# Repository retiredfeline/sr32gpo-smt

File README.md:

# Shift register 32 general purpose output board

These are the Kicad design files for the Shift register 32 bit general purpose output board described in my [Hackaday project page](https://hackaday.io/project/184239-3-line-to-32-line-output-expander).

## Versioning

SMT version February 2025

This version has been tested after assembly by PCBWay, who I thank for sponsoring a batch. You can find an uploaded project zip in the pcbway directory.

## Notes

The minimum lines required to use this board are: GND, SER (data), SRCLK (shift), RCLK (strobe). Vcc depends on the power arrangement. You should jumper the ~OESEL (output enable select) to ground if you don't wish to disable the display by signal, or vary the output with PWM, from a controller. The ~SRCLR input is only needed for resetting the output by the controller.

This board is designed with optional aspects you can choose to include or not:

- As mentioned some lines don't need to be driven in smaller configurations.

- Between 1 and 4 74HC595s can be installed for 8-32 outputs, in steps of 8. Naturally only the resistors for the used outputs need to be installed.

- The 74HC595 can source or sink 6 mA current.

- The 74HC595 can operate between 2V and 6V. This can be chosen to suit the controller, e.g. 3.3V or 5V, and the power supply section if installed.

- The power supply section is optional. You can choose to power this from the controller. Or you could power the controller with this.

- Copper pads for data and output are duplicated so you can attach more connectors or even solder wires. The input power is also brought out to duplicate pads for piggybacking to other circuits, e.g. an auxiliary board.

- Although the connectors are rendered as vertical pin headers, you can use other kinds of connectors like pin sockets, or even solder wires to the pads.

- You may wish to change the resistor to suit your application if you are getting the PCB assembled by editing the BoM. Currently it's set to 4.7k.

## Authors

* **Ken Yap**

## License

See the [LICENSE](LICENSE.md) file for license rights and limitations (MIT).

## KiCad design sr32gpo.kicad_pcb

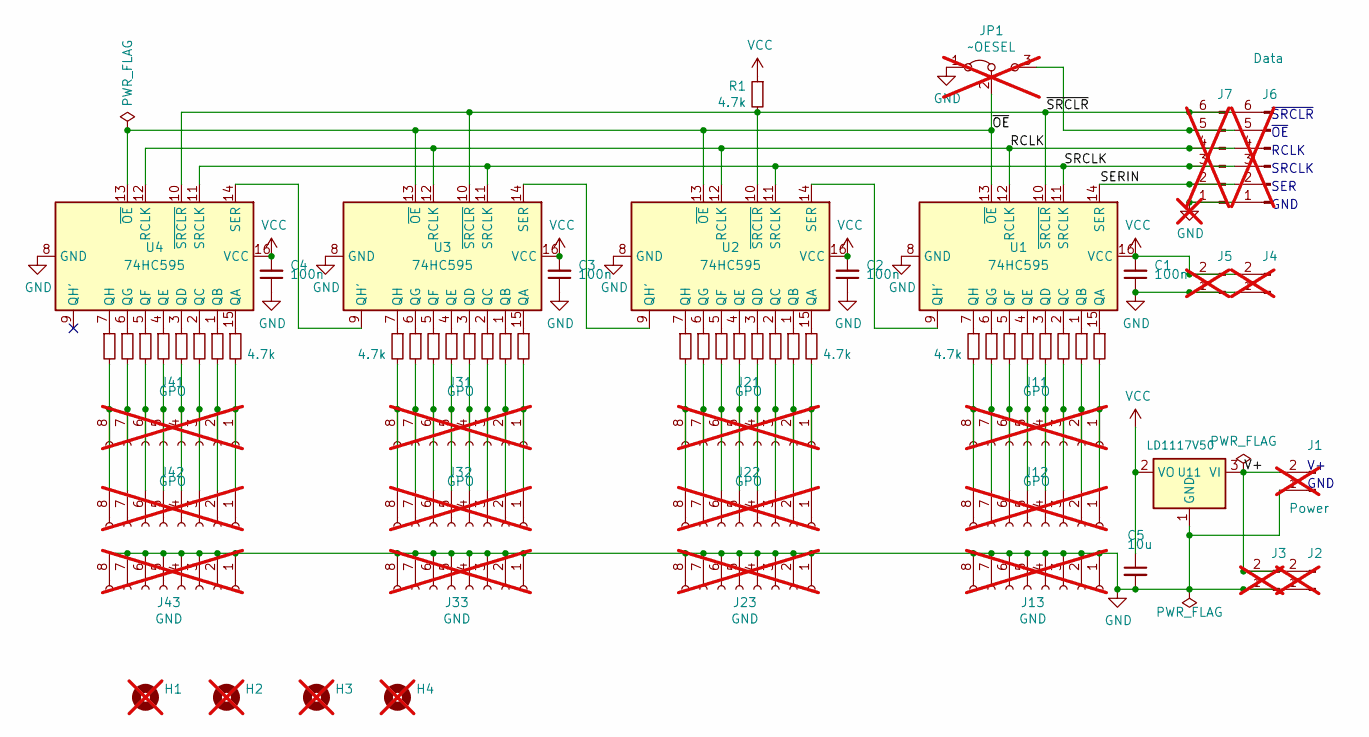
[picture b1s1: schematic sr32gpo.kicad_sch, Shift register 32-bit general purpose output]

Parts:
C1, C2, C3, C4: 100n; C_0603_1608Metric
C5: 10u; C_0805_2012Metric
H1, H2, H3, H4: MountingHole_3mm_Pad; not fitted
J1: Power; TerminalBlock_bornier-2_P5.08mm; not fitted
J2, J3, J4, J5: Power; PinHeader_1x02_P2.54mm_Vertical; not fitted
J6, J7: Data; PinHeader_1x06_P2.54mm_Vertical; not fitted
J11, J12, J21, J22, J31, J32, J41, J42: GPO; PinHeader_1x08_P2.54mm_Vertical; not fitted
J13, J23, J33, J43: GND; PinHeader_1x08_P2.54mm_Vertical; not fitted
JP1: ~OESEL; PinHeader_1x03_P2.54mm_Vertical; not fitted
R1, R11, R12, R13, R14, R15, R16, R17, R18, R21, R22, R23, R24, R25, R26, R27, R28, R31, R32, R33, R34, R35, R36, R37, R38, R41, R42, R43, R44, R45, R46, R47, R48: 4.7k; R_0603_1608Metric
U1, U2, U3, U4: 74HC595; SOIC-16_3.9x9.9mm_P1.27mm
U11: LD1117V50; SOT-223-3_TabPin2

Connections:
/RCLK: J6.4, J7.4, U1.12 (RCLK), U2.12 (RCLK), U3.12 (RCLK), U4.12 (RCLK)
/SERIN: J6.2, J7.2, U1.14 (SER)
/SRCLK: J6.3, J7.3, U1.11 (SRCLK), U2.11 (SRCLK), U3.11 (SRCLK), U4.11 (SRCLK)
/V+: J1.2, J2.2, J3.2, U11.3 (VI)
/~OE: JP1.2 (C), U1.13 (~OE), U2.13 (~OE), U3.13 (~OE), U4.13 (~OE)
/~SRCLR: J6.6, J7.6, R1.2, U1.10 (~SRCLR), U2.10 (~SRCLR), U3.10 (~SRCLR), U4.10 (~SRCLR)
GND: C1.1, C2.1, C3.1, C4.1, C5.2, J1.1, J2.1, J3.1, J4.1, J5.1, J6.1, J7.1, J13.1, J13.2, J13.3, J13.4, J13.5, J13.6, J13.7, J13.8, J23.1, J23.2, J23.3, J23.4, J23.5, J23.6, J23.7, J23.8, J33.1, J33.2, J33.3, J33.4, J33.5, J33.6, J33.7, J33.8, J43.1, J43.2, J43.3, J43.4, J43.5, J43.6, J43.7, J43.8, JP1.1 (A), U1.8 (GND), U2.8 (GND), U3.8 (GND), U4.8 (GND), U11.1 (GND)
unnamed: J6.5, J7.5, JP1.3 (B)
unnamed: J11.1, J12.1, R11.2
unnamed: J11.2, J12.2, R12.2
unnamed: J11.3, J12.3, R13.2
unnamed: J11.4, J12.4, R14.2
unnamed: J11.5, J12.5, R15.2
unnamed: J11.6, J12.6, R16.2
unnamed: J11.7, J12.7, R17.2
unnamed: J11.8, J12.8, R18.2
unnamed: J21.1, J22.1, R21.2
unnamed: J21.2, J22.2, R22.2
unnamed: J21.3, J22.3, R23.2
unnamed: J21.4, J22.4, R24.2
unnamed: J21.5, J22.5, R25.2
unnamed: J21.6, J22.6, R26.2
unnamed: J21.7, J22.7, R27.2
unnamed: J21.8, J22.8, R28.2
unnamed: J31.1, J32.1, R31.2
unnamed: J31.2, J32.2, R32.2
unnamed: J31.3, J32.3, R33.2
unnamed: J31.4, J32.4, R34.2
unnamed: J31.5, J32.5, R35.2
unnamed: J31.6, J32.6, R36.2
unnamed: J31.7, J32.7, R37.2
unnamed: J31.8, J32.8, R38.2
unnamed: J41.1, J42.1, R41.2
unnamed: J41.2, J42.2, R42.2
unnamed: J41.3, J42.3, R43.2
unnamed: J41.4, J42.4, R44.2
unnamed: J41.5, J42.5, R45.2
unnamed: J41.6, J42.6, R46.2
unnamed: J41.7, J42.7, R47.2
unnamed: J41.8, J42.8, R48.2
unnamed: R11.1, U1.15 (QA)
unnamed: R12.1, U1.1 (QB)
unnamed: R13.1, U1.2 (QC)
unnamed: R14.1, U1.3 (QD)
unnamed: R15.1, U1.4 (QE)
unnamed: R16.1, U1.5 (QF)
unnamed: R17.1, U1.6 (QG)
unnamed: U1.9 (QH'), U2.14 (SER)
unnamed: R18.1, U1.7 (QH)
unnamed: R21.1, U2.15 (QA)
unnamed: R22.1, U2.1 (QB)
unnamed: R23.1, U2.2 (QC)
unnamed: R24.1, U2.3 (QD)
unnamed: R25.1, U2.4 (QE)
unnamed: R26.1, U2.5 (QF)
unnamed: R27.1, U2.6 (QG)
unnamed: U2.9 (QH'), U3.14 (SER)
unnamed: R28.1, U2.7 (QH)
unnamed: R31.1, U3.15 (QA)
unnamed: R32.1, U3.1 (QB)
unnamed: R33.1, U3.2 (QC)
unnamed: R34.1, U3.3 (QD)
unnamed: R35.1, U3.4 (QE)
unnamed: R36.1, U3.5 (QF)
unnamed: R37.1, U3.6 (QG)
unnamed: U3.9 (QH'), U4.14 (SER)
unnamed: R38.1, U3.7 (QH)
unnamed: R41.1, U4.15 (QA)
unnamed: R42.1, U4.1 (QB)
unnamed: R43.1, U4.2 (QC)
unnamed: R44.1, U4.3 (QD)
unnamed: R45.1, U4.4 (QE)
unnamed: R46.1, U4.5 (QF)
unnamed: R47.1, U4.6 (QG)
unnamed: R48.1, U4.7 (QH)
VCC: C1.2, C2.2, C3.2, C4.2, C5.1, J4.2, J5.2, R1.1, U1.16 (VCC), U2.16 (VCC), U3.16 (VCC), U4.16 (VCC), U11.2 (VO)

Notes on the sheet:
RCLK
SRCLK
GND
~{OE}
~{SRCLR}
SER

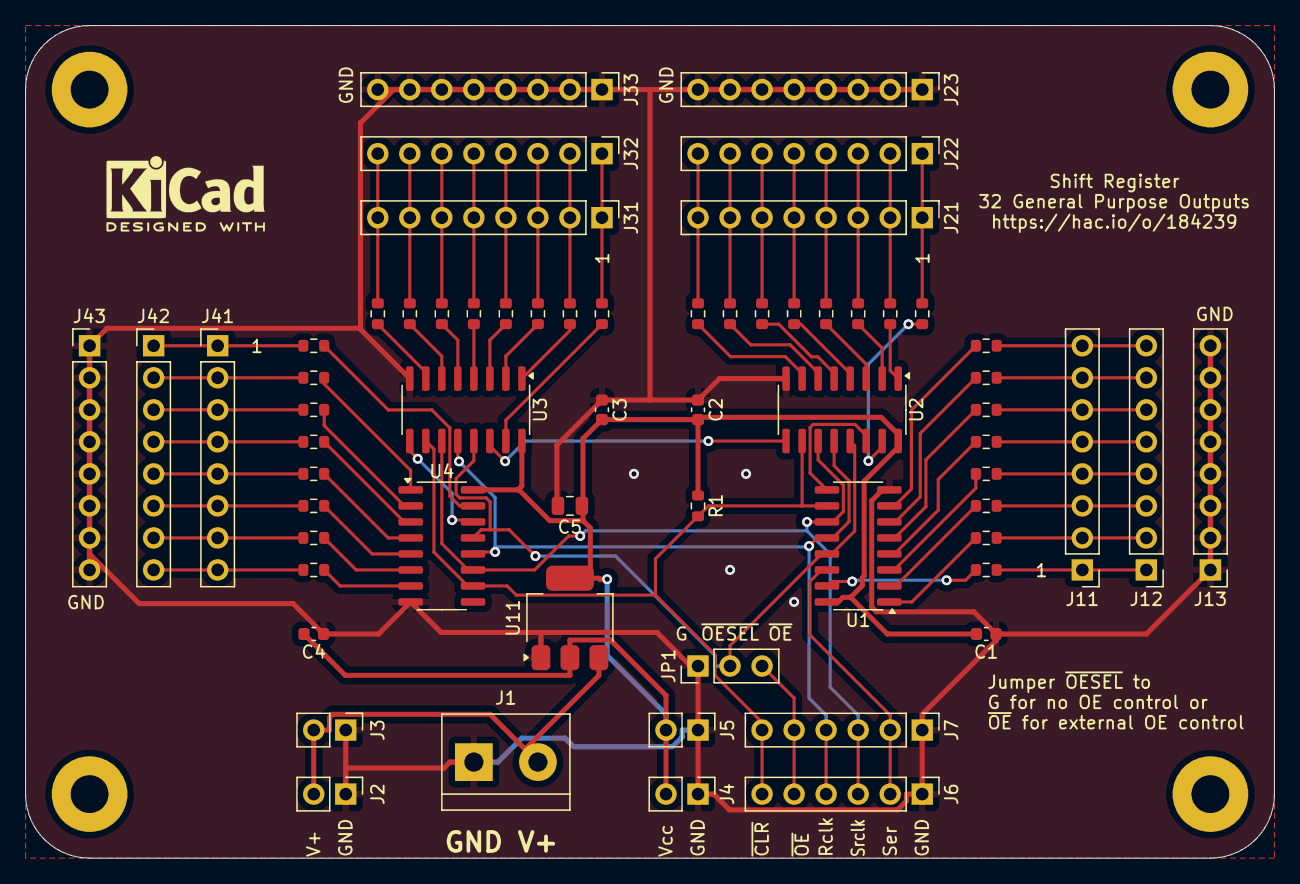
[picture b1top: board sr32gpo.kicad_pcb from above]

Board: 2 copper layers, 99.1 x 66.0 mm, 67 parts (0 on the bottom side), 76 nets.

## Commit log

2022-07-20 Initial release
2022-09-12 Redo with updated SOIC-16 footprint, better GND planes, and tentative fields for PCBWay assembly. Unverified.
2025-02-06 Update to KiCad v8, improve silkscreen, generate BOM and POS files for PCBWay
2025-02-06 Update gerbers too
